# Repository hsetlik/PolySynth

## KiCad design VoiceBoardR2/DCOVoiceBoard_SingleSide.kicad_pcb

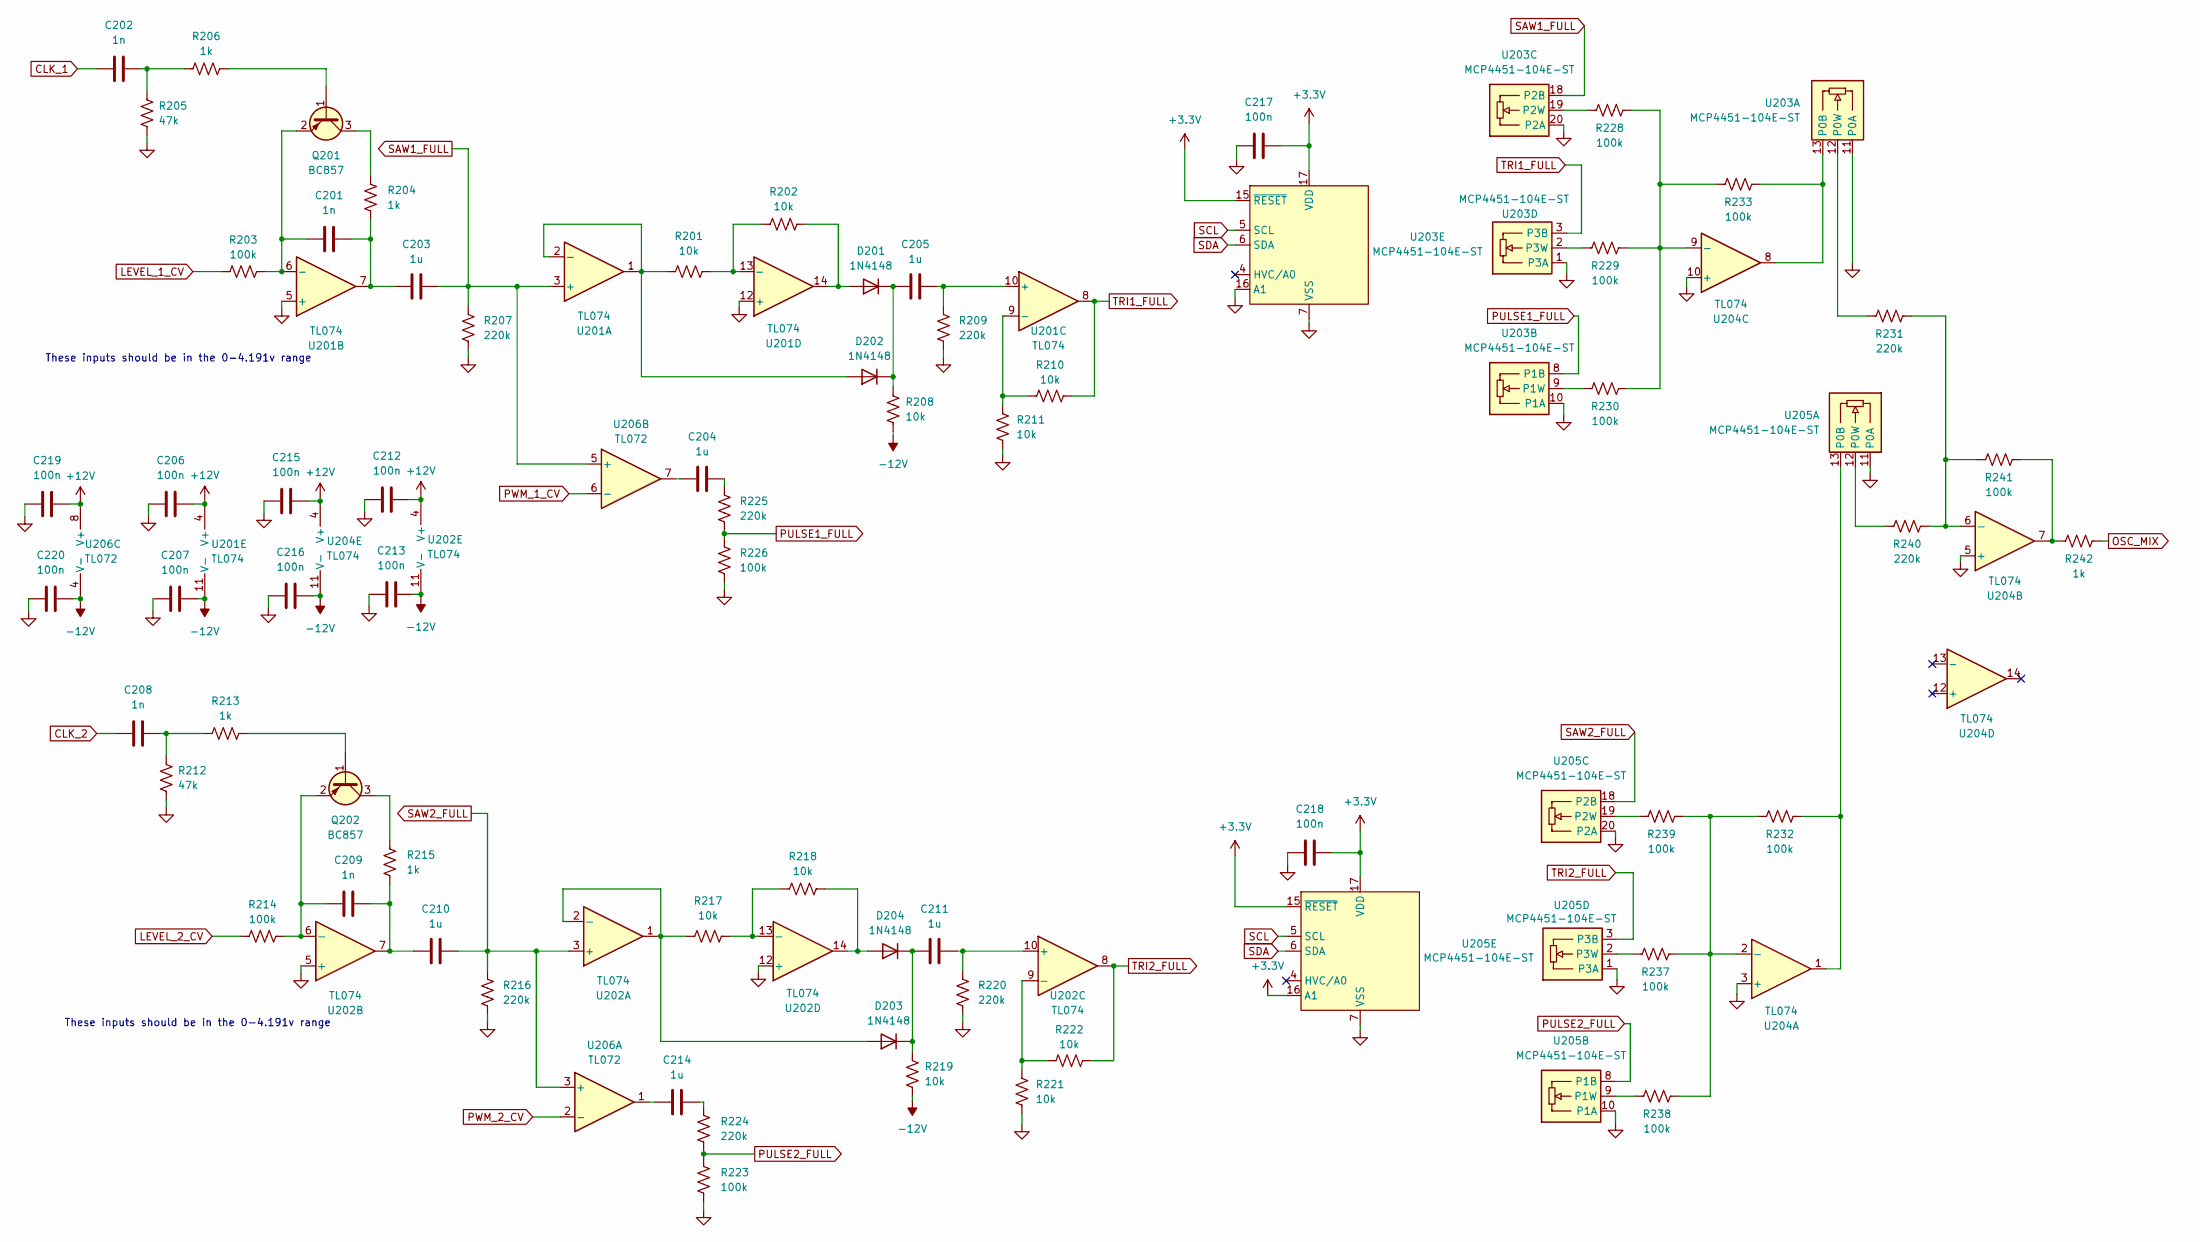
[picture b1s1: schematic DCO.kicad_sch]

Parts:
C201, C202, C208, C209: 1n; C_0805_2012Metric
C203, C204, C205, C210, C211, C214: 1u; C_0805_2012Metric
C206, C207, C212, C213, C215, C216, C217, C218, C219, C220: 100n; C_0805_2012Metric
D201, D202, D203, D204: 1N4148; D_0805_2012Metric
Q201, Q202: BC857; SOT-23
R201, R202, R208, R210, R211, R217, R218, R219, R221, R222: 10k; R_0805_2012Metric
R203, R214, R223, R226, R228, R229, R230, R232, R233, R237, R238, R239, R241: 100k; R_0805_2012Metric
R204, R206, R213, R215, R242: 1k; R_0805_2012Metric
R205, R212: 47k; R_0805_2012Metric
R207, R209, R216, R220, R224, R225, R231, R240: 220k; R_0805_2012Metric
U201, U202, U204: TL074; SOIC-14_3.9x8.7mm_P1.27mm
U203, U205: MCP4451-104E-ST; TSSOP-20_4.4x6.5mm_P0.65mm
U206: TL072; SOIC-8_3.9x4.9mm_P1.27mm

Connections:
+12V: C206.2, C212.2, C215.2, C219.2, U201.4 (V+), U202.4 (V+), U204.4 (V+), U206.8 (V+); also elsewhere on the board
-12V: C207.2, C213.2, C216.2, C220.2, R208.1, R219.1, U201.11 (V-), U202.11 (V-), U204.11 (V-), U206.4 (V-); also elsewhere on the board
CLK_1: C202.1; also elsewhere on the board
CLK_2: C208.1; also elsewhere on the board
GND: C206.1, C207.1, C212.1, C213.1, C215.1, C216.1, C217.1, C218.1, C219.1, C220.1, R205.1, R207.2, R209.2, R211.1, R212.1, R216.2, R220.2, R221.1, R223.2, R226.2, U201.5 (+), U201.12 (+), U202.5 (+), U202.12 (+), U203.1 (P3A), U203.7 (VSS), U203.10 (P1A), U203.11 (P0A), U203.16 (A1), U203.20 (P2A), U204.3 (+), U204.5 (+), U204.10 (+), U205.1 (P3A), U205.7 (VSS), U205.10 (P1A), U205.11 (P0A), U205.20 (P2A); also elsewhere on the board
LEVEL_1_CV: R203.1; also elsewhere on the board
LEVEL_2_CV: R214.1; also elsewhere on the board
unnamed: C201.2, C203.1, R204.1, U201.7
unnamed: C202.2, R205.2, R206.2
unnamed: C204.1, U206.7
unnamed: C204.2, R225.1
unnamed: C208.2, R212.2, R213.2
unnamed: C209.2, C210.1, R215.1, U202.7
unnamed: C214.1, U206.1
unnamed: C214.2, R224.1
unnamed: D201.2 (A), R202.2, U201.14
unnamed: C205.1, D201.1 (K), D202.1 (K), R208.2
unnamed: D202.2 (A), R201.1, U201.1, U201.2 (-)
unnamed: D203.2 (A), R217.1, U202.1, U202.2 (-)
unnamed: C211.1, D203.1 (K), D204.1 (K), R219.2
unnamed: D204.2 (A), R218.2, U202.14
unnamed: Q201.1 (B), R206.1
unnamed: Q201.3 (C), R204.2
unnamed: C201.1, Q201.2 (E), R203.2, U201.6 (-)
unnamed: Q202.1 (B), R213.1
unnamed: Q202.3 (C), R215.2
unnamed: C209.1, Q202.2 (E), R214.2, U202.6 (-)
unnamed: R241.2, R242.1, U204.7
unnamed: C205.2, R209.1, U201.10 (+)
unnamed: R210.1, R211.2, U201.9 (-)
unnamed: R201.2, R202.1, U201.13 (-)
unnamed: C211.2, R220.1, U202.10 (+)
unnamed: R221.2, R222.1, U202.9 (-)
unnamed: R217.2, R218.1, U202.13 (-)
unnamed: R233.2, U203.13 (P0B), U204.8
unnamed: R231.1, U203.12 (P0W)
unnamed: R230.1, U203.9 (P1W)
unnamed: R228.1, U203.19 (P2W)
unnamed: R229.1, U203.2 (P3W)
unnamed: R232.1, R237.2, R238.2, R239.2, U204.2 (-)
unnamed: R231.2, R240.2, R241.1, U204.6 (-)
unnamed: R228.2, R229.2, R230.2, R233.1, U204.9 (-)
unnamed: R232.2, U204.1, U205.13 (P0B)
unnamed: R240.1, U205.12 (P0W)
unnamed: R238.1, U205.9 (P1W)
unnamed: R239.1, U205.19 (P2W)
unnamed: R237.1, U205.2 (P3W)
OSC_MIX: R242.2; also elsewhere on the board
PULSE1_FULL: R225.2, R226.1, U203.8 (P1B)
PULSE2_FULL: R223.1, R224.2, U205.8 (P1B)
PWM_1_CV: U206.6 (-); also elsewhere on the board
PWM_2_CV: U206.2 (-); also elsewhere on the board
SAW1_FULL: C203.2, R207.1, U201.3 (+), U203.18 (P2B), U206.5 (+)
SAW2_FULL: C210.2, R216.1, U202.3 (+), U205.18 (P2B), U206.3 (+)
SCL: U203.5 (SCL), U205.5 (SCL); also elsewhere on the board
SDA: U203.6 (SDA), U205.6 (SDA); also elsewhere on the board
TRI1_FULL: R210.2, U201.8, U203.3 (P3B)
TRI2_FULL: R222.2, U202.8, U205.3 (P3B)

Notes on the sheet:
These inputs should be in the 0-4.191v range

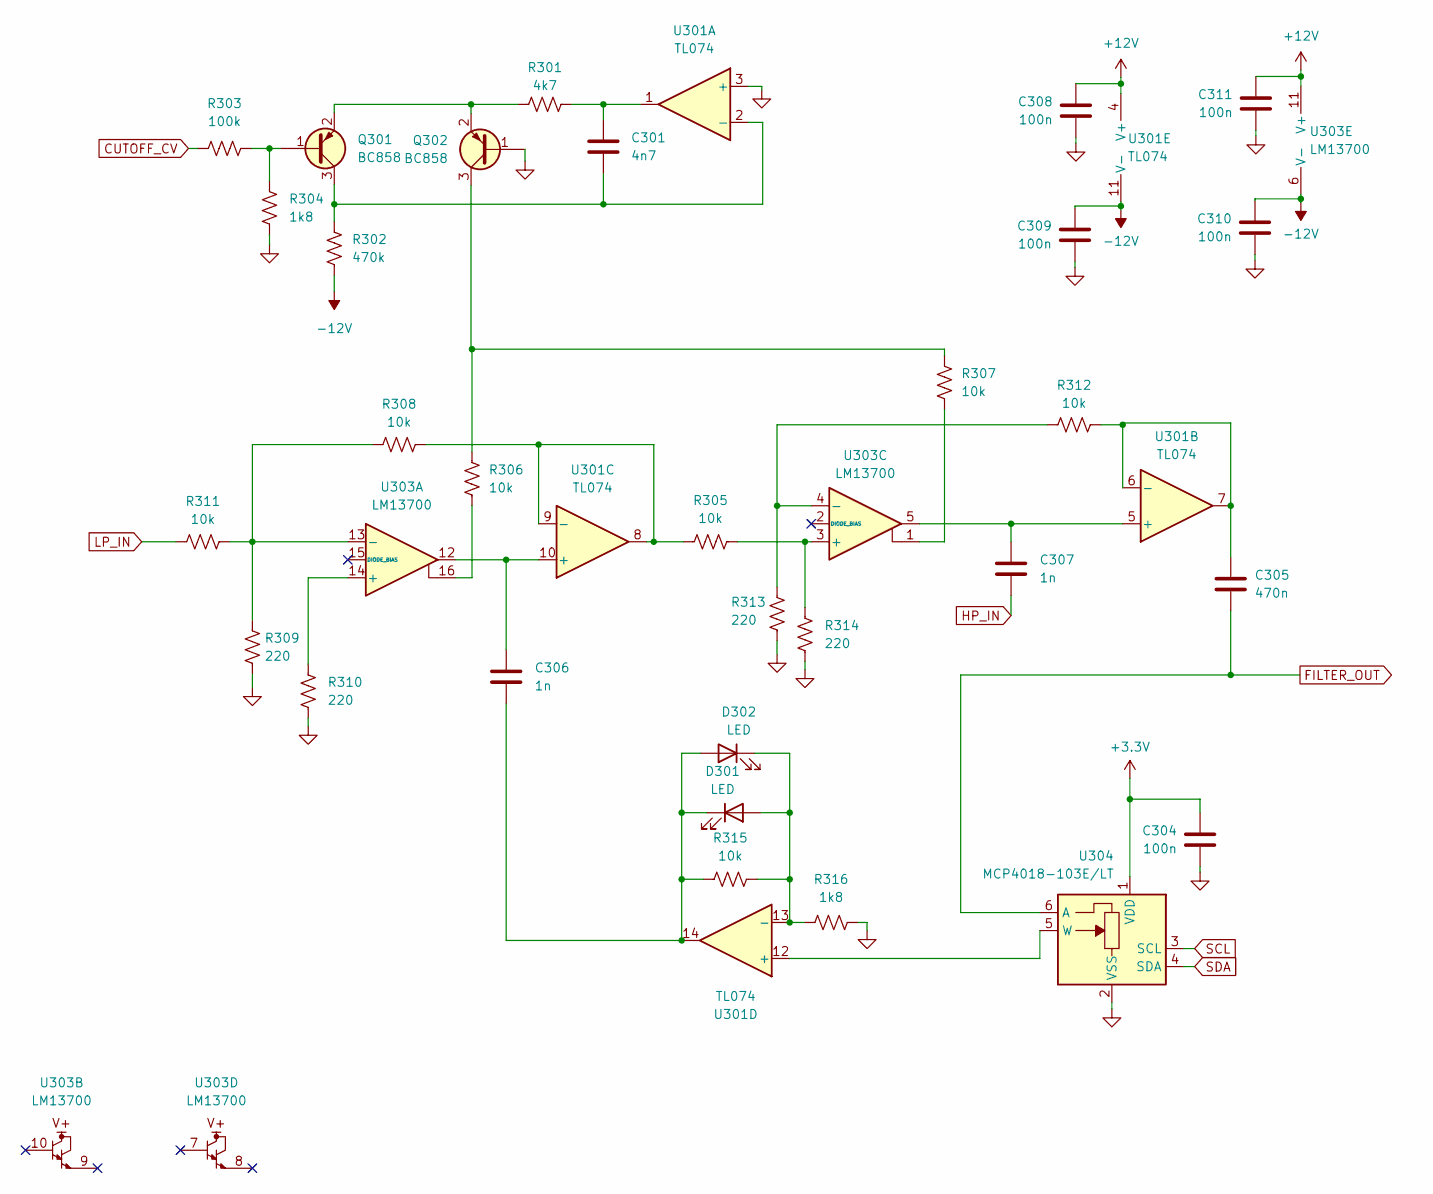
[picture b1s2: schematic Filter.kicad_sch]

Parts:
C301: 4n7; C_0805_2012Metric
C304, C308, C309, C310, C311: 100n; C_0805_2012Metric
C305: 470n; C_0805_2012Metric
C306, C307: 1n; C_0805_2012Metric
D301, D302: LED; LED_0805_2012Metric
Q301, Q302: BC858; SOT-23
R301: 4k7; R_0805_2012Metric
R302: 470k; R_0805_2012Metric
R303: 100k; R_0805_2012Metric
R304, R316: 1k8; R_0805_2012Metric
R305, R306, R307, R308, R311, R312, R315: 10k; R_0805_2012Metric
R309, R310, R313, R314: 220; R_0805_2012Metric
U301: TL074; SOIC-14_3.9x8.7mm_P1.27mm
U303: LM13700; SOIC-16_3.9x9.9mm_P1.27mm
U304: MCP4018-103E/LT; SOT-363_SC-70-6

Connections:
+12V: C308.1, C311.1, U301.4 (V+), U303.11 (V+); also elsewhere on the board
-12V: C309.1, C310.1, R302.1, U301.11 (V-), U303.6 (V-); also elsewhere on the board
CUTOFF_CV: R303.2; also elsewhere on the board
FILTER_OUT: C305.2, U304.6 (A); also elsewhere on the board
GND: C304.2, C308.2, C309.2, C310.2, C311.2, Q302.1 (B), R304.2, R309.1, R310.1, R313.1, R314.1, R316.1, U301.3 (+), U304.2 (VSS); also elsewhere on the board
HP_IN: C307.2; also elsewhere on the board
LP_IN: R311.1; also elsewhere on the board
unnamed: C301.1, R301.2, U301.1
unnamed: D301.2 (A), D302.1 (K), R315.1, R316.2, U301.13 (-)
unnamed: C306.2, D301.1 (K), D302.2 (A), R315.2, U301.14
unnamed: Q301.1 (B), R303.1, R304.1
unnamed: C301.2, Q301.3 (C), R302.2, U301.2 (-)
unnamed: Q301.2 (E), Q302.2 (E), R301.1
unnamed: Q302.3 (C), R306.1, R307.1
unnamed: R306.2, U303.16
unnamed: R307.2, U303.1
unnamed: C307.1, U301.5 (+), U303.5
unnamed: C305.1, R312.2, U301.6 (-), U301.7
unnamed: C306.1, U301.10 (+), U303.12
unnamed: R305.2, R308.2, U301.8, U301.9 (-)
unnamed: U301.12 (+), U304.5 (W)
unnamed: R310.2, U303.14 (+)
unnamed: R308.1, R309.2, R311.2, U303.13 (-)
unnamed: R305.1, R314.2, U303.3 (+)
unnamed: R312.1, R313.2, U303.4 (-)
SCL: U304.3 (SCL); also elsewhere on the board
SDA: U304.4 (SDA); also elsewhere on the board

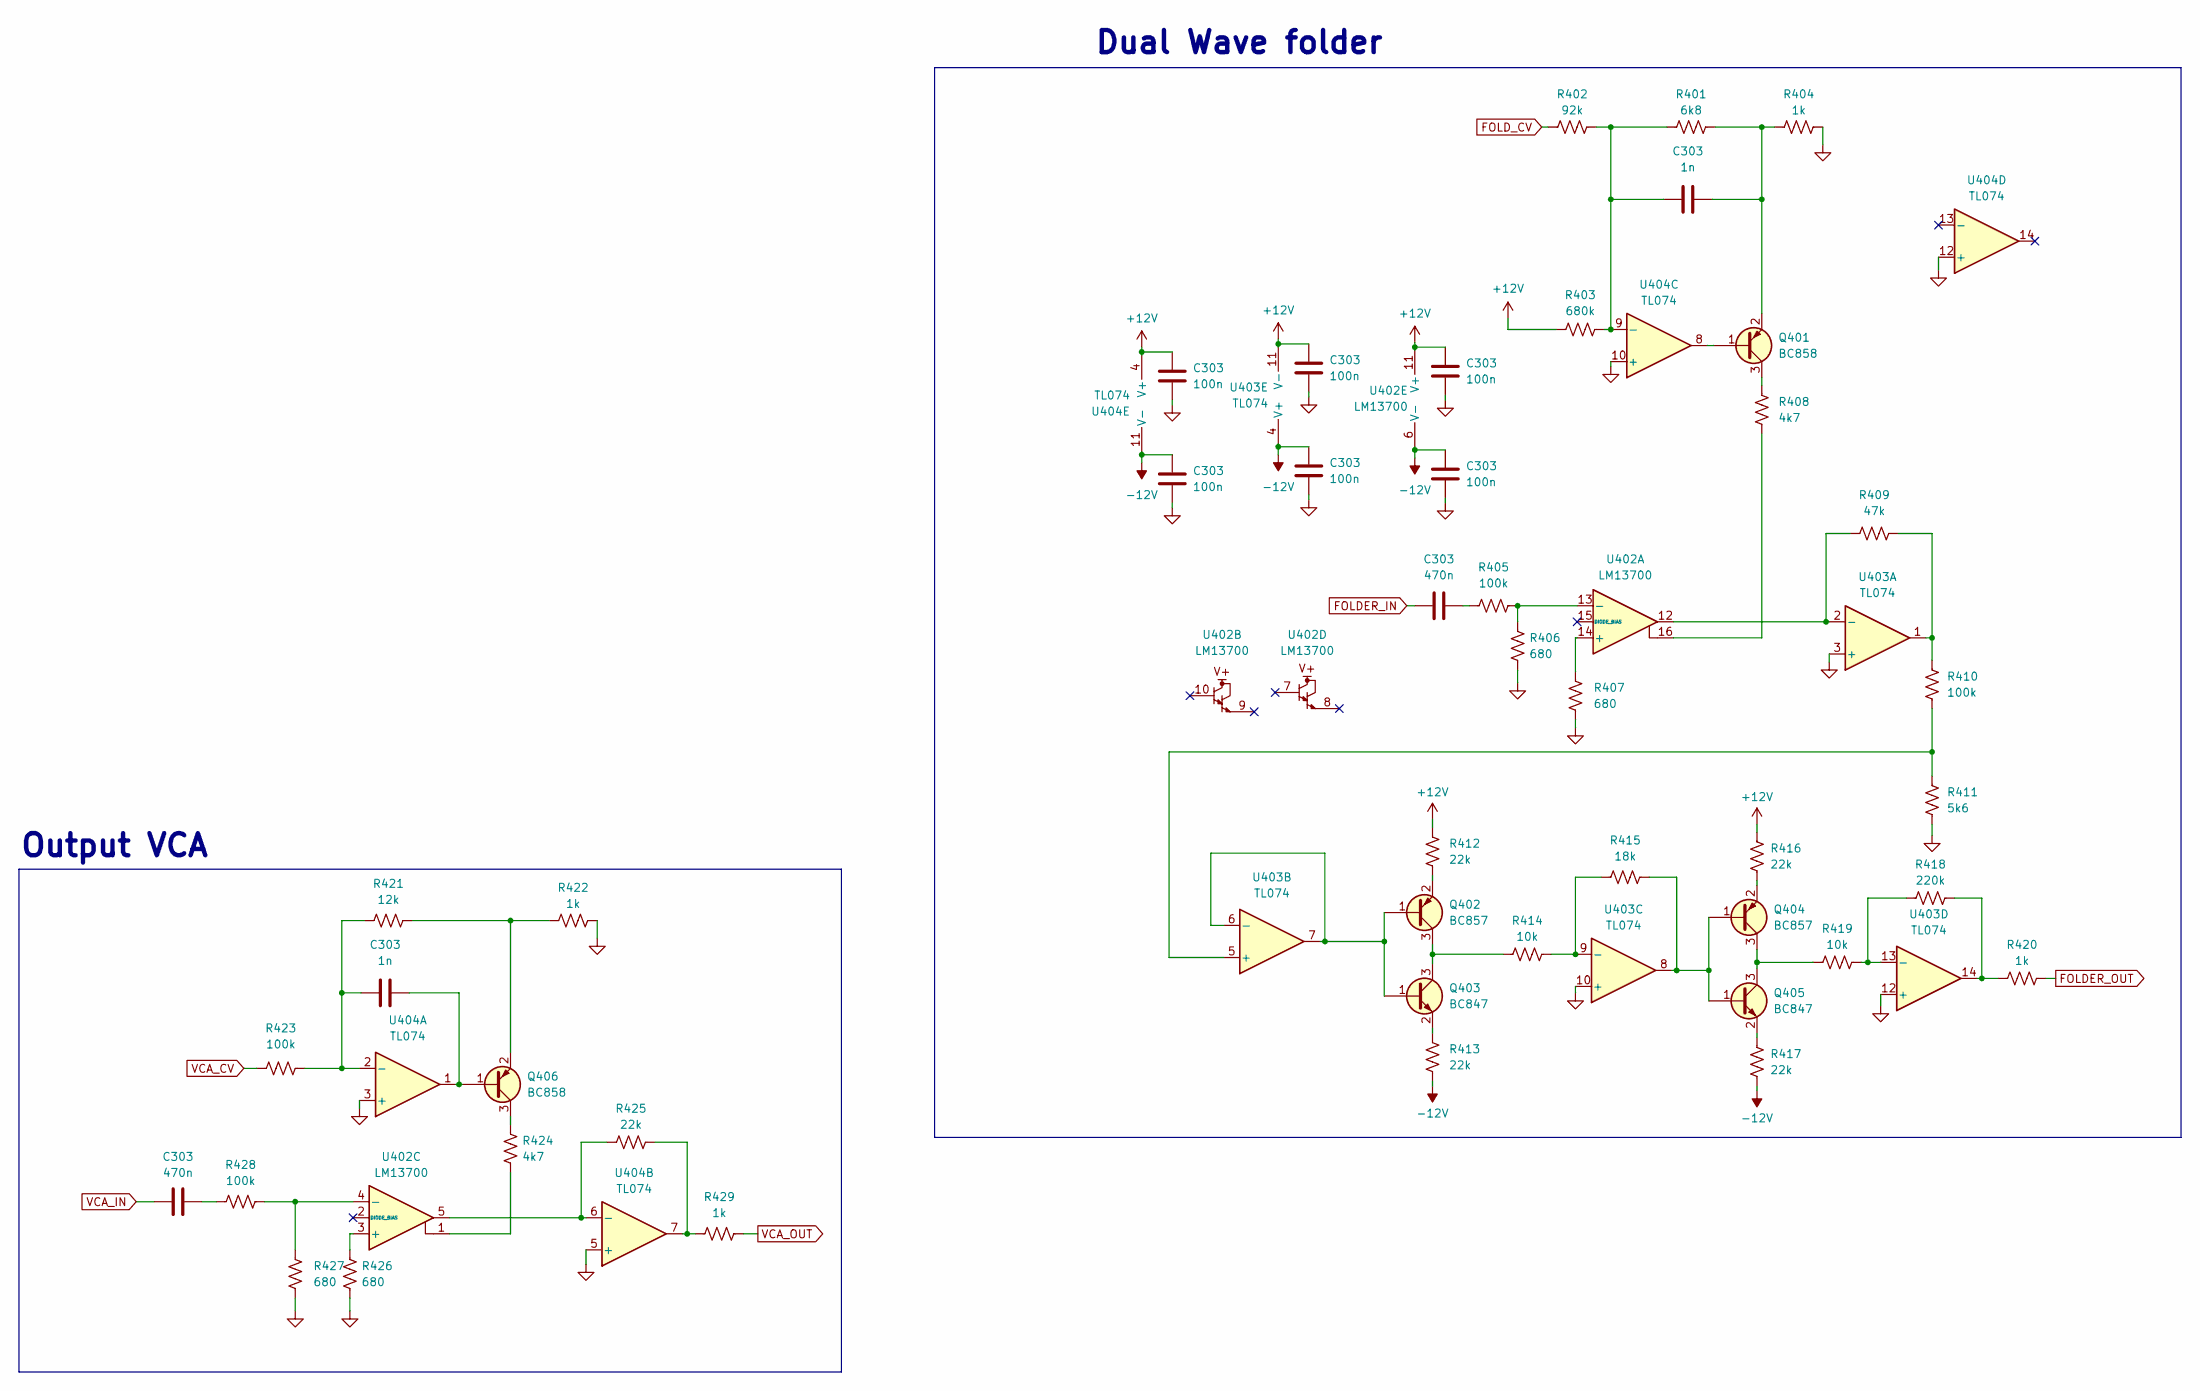
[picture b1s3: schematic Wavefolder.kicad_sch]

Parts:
C303: 100n; C_0805_2012Metric
Q401, Q406: BC858; SOT-23
Q402, Q404: BC857; SOT-23
Q403, Q405: BC847; SOT-23
R401: 6k8; R_0805_2012Metric
R402: 92k; R_0805_2012Metric
R403: 680k; R_0805_2012Metric
R404, R420, R422, R429: 1k; R_0805_2012Metric
R405, R410, R423, R428: 100k; R_0805_2012Metric
R406, R407, R426, R427: 680; R_0805_2012Metric
R408, R424: 4k7; R_0805_2012Metric
R409: 47k; R_0805_2012Metric
R411: 5k6; R_0805_2012Metric
R412, R413, R416, R417, R425: 22k; R_0805_2012Metric
R414, R419: 10k; R_0805_2012Metric
R415: 18k; R_0805_2012Metric
R418: 220k; R_0805_2012Metric
R421: 12k; R_0805_2012Metric
U402: LM13700; SOIC-16_3.9x9.9mm_P1.27mm
U403, U404: TL074; SOIC-14_3.9x8.7mm_P1.27mm

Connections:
+12V: R403.1, R412.2, R416.2, U402.11 (V+), U403.11 (V-), U404.4 (V+); also elsewhere on the board
-12V: R413.1, R417.1, U402.6 (V-), U403.4 (V+), U404.11 (V-); also elsewhere on the board
FOLDER_OUT: R420.1; also elsewhere on the board
FOLD_CV: R402.1; also elsewhere on the board
GND: R404.2, R406.1, R407.1, R411.2, R422.2, R426.1, R427.1, U403.3 (+), U403.10 (+), U403.12 (+), U404.3 (+), U404.5 (+), U404.10 (+), U404.12 (+); also elsewhere on the board
unnamed 26: R405.1; also elsewhere on the board
unnamed 27: R428.2; also elsewhere on the board
unnamed: Q401.1 (B), U404.8
unnamed: Q401.3 (C), R408.2
unnamed 48: Q401.2 (E), R401.2, R404.1; also elsewhere on the board
unnamed: Q402.1 (B), Q403.1 (B), U403.6 (-), U403.7
unnamed: Q402.3 (C), Q403.3 (C), R414.2
unnamed: Q402.2 (E), R412.1
unnamed: Q403.2 (E), R413.2
unnamed: Q404.1 (B), Q405.1 (B), R415.1, U403.8
unnamed: Q404.3 (C), Q405.3 (C), R419.2
unnamed: Q404.2 (E), R416.1
unnamed: Q405.2 (E), R417.2
unnamed 57: Q406.1 (B), U404.1; also elsewhere on the board
unnamed: Q406.3 (C), R424.2
unnamed: Q406.2 (E), R421.2, R422.1
unnamed: R408.1, U402.16
unnamed: R409.1, R410.1, U403.1
unnamed: R418.1, R420.2, U403.14
unnamed: R424.1, U402.1
unnamed: R425.2, R429.1, U404.7
unnamed: R407.2, U402.14 (+)
unnamed: R405.2, R406.2, U402.13 (-)
unnamed: R426.2, U402.3 (+)
unnamed: R427.2, R428.1, U402.4 (-)
unnamed: R409.2, U402.12, U403.2 (-)
unnamed: R410.2, R411.1, U403.5 (+)
unnamed: R414.1, R415.2, U403.9 (-)
unnamed: R418.2, R419.1, U403.13 (-)
unnamed 104: R421.1, R423.2, U404.2 (-); also elsewhere on the board
unnamed: R425.1, U402.5, U404.6 (-)
unnamed 106: R401.1, R402.2, R403.2, U404.9 (-); also elsewhere on the board
VCA_CV: R423.1; also elsewhere on the board
VCA_OUT: R429.2; also elsewhere on the board

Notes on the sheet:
Dual Wave folder
Output VCA

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
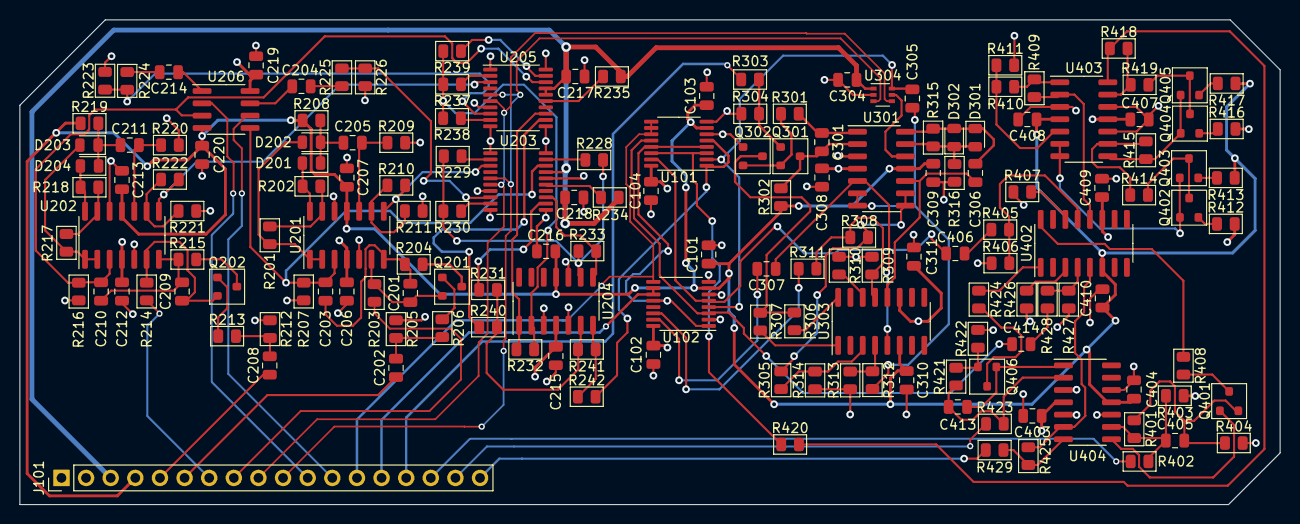
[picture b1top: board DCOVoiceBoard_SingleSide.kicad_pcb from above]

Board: 4 copper layers, 130.0 x 50.0 mm, 159 parts (0 on the bottom side), 124 nets.

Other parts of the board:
C101, C102, C103, C104, C403, C404, C407, C408, C409, C410: 100n; C_0805_2012Metric
C405, C413: 1n; C_0805_2012Metric
C406, C414: 470n; C_0805_2012Metric
J101: VoiceHeader; PinHeader_1x18_P2.54mm_Vertical
R234, R235: 10k; R_0805_2012Metric
U101, U102: TMUX4053; TSSOP-16_4.4x5mm_P0.65mm

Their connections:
+12V: C102.1, C104.1, C403.1, C407.1, C409.1, J101.2 (+12V), U101.16 (VDD), U102.16 (VDD); also elsewhere on the board
-12V: C101.1, C103.1, C404.1, C408.1, C410.1, J101.4 (-12V), U101.7 (VSS), U102.7 (VSS); also elsewhere on the board
CLK_1: J101.6 (CLK1); also elsewhere on the board
CLK_2: J101.5 (CLK2); also elsewhere on the board
CUTOFF_CV: J101.15 (CutoffCV); also elsewhere on the board
FILTER_IN: U101.4 (C), U101.13 (A1), U102.1 (B1), U102.12 (A0)
FILTER_OUT: U101.2 (B0), U102.4 (C); also elsewhere on the board
FOLDER_IN: C406.1, U101.15 (B), U102.5 (C0)
FOLDER_OUT: U101.3 (C1), U101.14 (A); also elsewhere on the board
FOLD_CV: J101.16 (FoldCV); also elsewhere on the board
FOLD_FIRST: J101.13 (FoldFirst), U101.9 (S3), U101.10 (S2), U101.11 (S1), U102.9 (S3)
GND: C101.2, C102.2, C103.2, C104.2, C403.2, C404.2, C407.2, C408.2, C409.2, C410.2, J101.1 (GND), U101.6 (INH), U101.8 (GND), U102.2 (B0), U102.6 (INH), U102.8 (GND); also elsewhere on the board
HP_IN: U102.15 (B); also elsewhere on the board
HP_MODE: J101.14 (HiPass), U102.10 (S2), U102.11 (S1)
LEVEL_1_CV: J101.8 (L1); also elsewhere on the board
LEVEL_2_CV: J101.7 (L2); also elsewhere on the board
LP_IN: U102.14 (A); also elsewhere on the board
unnamed 26: C406.2; also elsewhere on the board
unnamed 27: C414.2; also elsewhere on the board
unnamed 48: C405.2; also elsewhere on the board
unnamed 57: C413.2; also elsewhere on the board
unnamed 104: C413.1; also elsewhere on the board
unnamed 106: C405.1; also elsewhere on the board
OSC_MIX: U101.1 (B1), U101.5 (C0); also elsewhere on the board
PWM_1_CV: J101.12 (PWM1); also elsewhere on the board
PWM_2_CV: J101.11 (PWM2); also elsewhere on the board
SCL: J101.10 (SCL); also elsewhere on the board
SDA: J101.9 (SDA); also elsewhere on the board
VCA_CV: J101.17 (AmpCV); also elsewhere on the board
VCA_IN: C414.1, U101.12 (A0), U102.3 (C1)
VCA_OUT: J101.18 (VoiceOut); also elsewhere on the board
